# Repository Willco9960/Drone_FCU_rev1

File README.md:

# Drone MCU

I'm building a drone flight controller from scratch and using it to explore neural networks along the way. The long-term goal is a small autonomous drone that can track a person, follow them and orbit around them. First though, I need a board that works on my desk and tells me which way is up.

This is a university project and a work in progress.

## How I built it

I designed and routed the board myself in KiCad. I also used an AI agent connected through an MCP to help choose parts and check the schematic and routing as I went.

## The plan

V1 is a USB-powered development board built around an STM32H743 and an IMU, the sensor that measures movement and rotation. The idea is to read that sensor on the board, send live data to a computer and show the board's orientation in a window.

I also want to train a small neural network in simulation and run it on the MCU. The computer will show what the sensor is doing alongside the network's predicted correction so I can see what it's learning before motors get involved.

The V1 testbench board is currently in production. Once it arrives, I'll start testing it on the bench. It doesn't control motors or fly. Later versions will need flight hardware, reliable stabilization, a camera, tracking and plenty of testing before they become the autonomous drone I'm aiming for.

## Where things are

- [Drone_MCU_V1](Drone_MCU_V1/) has the current KiCad project. Open [Drone_MCU_V1.kicad_pro](Drone_MCU_V1/Drone_MCU_V1.kicad_pro) to see the schematic and PCB.
- [V1 plan](Drone_MCU_V1/V1_PLAN.md) explains the goals and the work still to do.
- [Manufacturing and assembly files](Drone_MCU_V1/manufacturing/2026-11-08-quote/) contain the quote files, parts list and assembly research. The files in this folder are marked quote only, so check the review before using them for an order.
- [Reviews](Drone_MCU_V1/reviews/) contain saved design checks and notes from the board review.
- [REV_1](REV_1/) is the earlier flight controller design. I'm keeping it around as a reference while V1 gets its own fresh start.

[DECISIONS.md](DECISIONS.md) keeps the project decisions and open questions. [AGENTS.md](AGENTS.md) has context for anyone using an AI agent to help with the project.

## PCB images

Here's a look at the V1 board in KiCad before it heads to the bench.

## What's next

Test the board when it arrives, read the IMU, stream the data to a computer and build the live orientation display. After that it's time to get a neural network trained in simulation and see what the MCU can do with it.

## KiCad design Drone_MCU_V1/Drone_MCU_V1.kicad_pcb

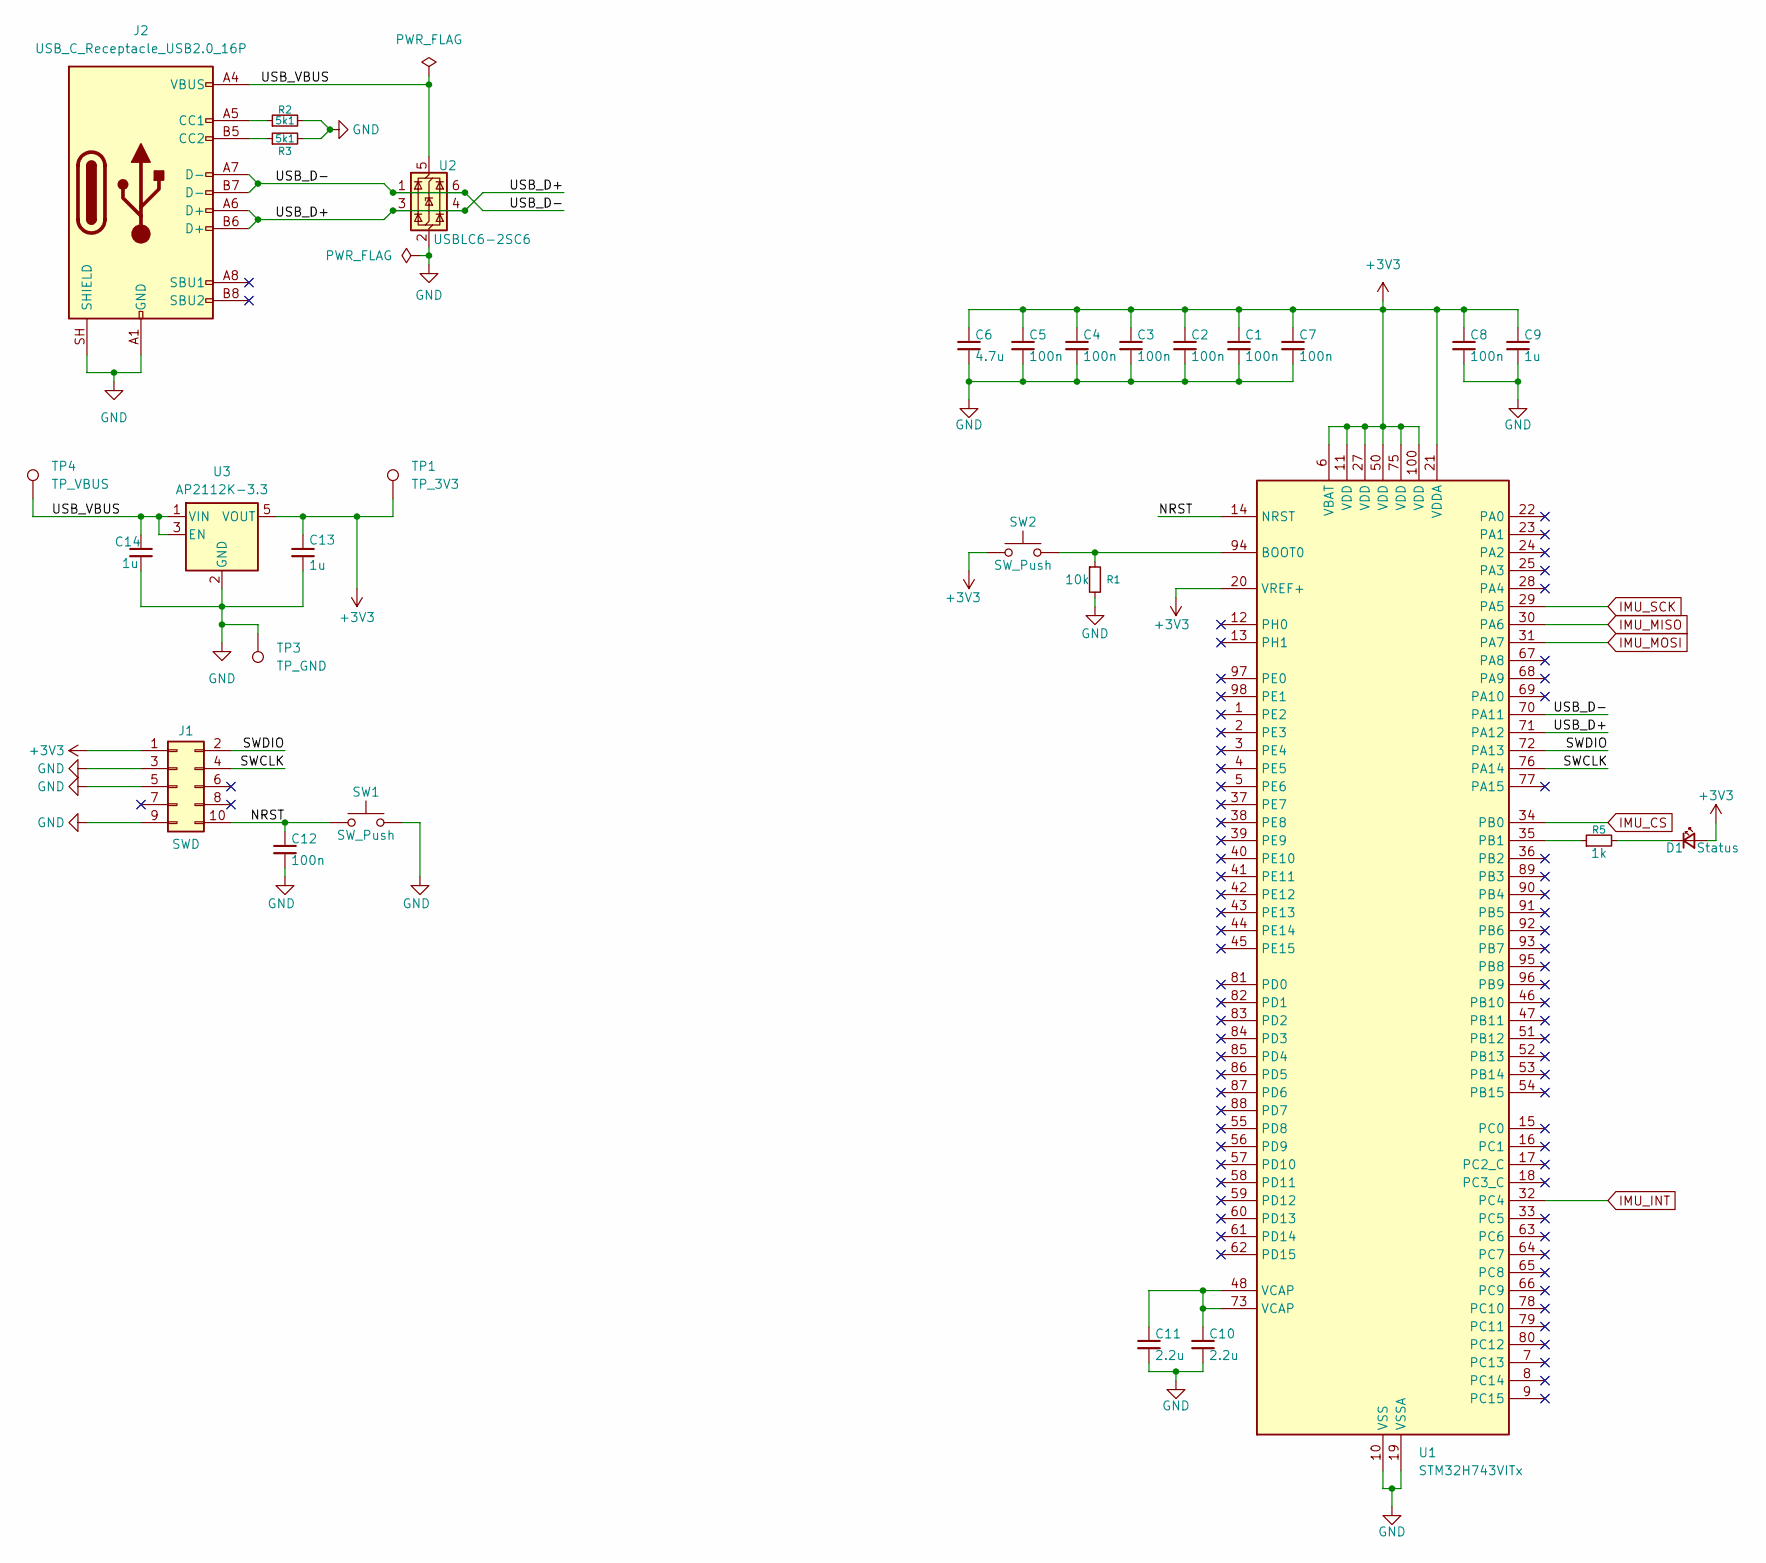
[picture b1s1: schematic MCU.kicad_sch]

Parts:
C1, C2, C3, C4, C5, C7, C8, C12: 100n; C_0805_2012Metric
C6: 4.7u; C_1206_3216Metric
C9, C13, C14: 1u; C_0805_2012Metric
C10, C11: 2.2u; C_1206_3216Metric
D1: Status; LED_0805_2012Metric
J1: SWD; PinHeader_2x05_P2.54mm_Vertical
J2: USB_C_Receptacle_USB2.0_16P; USB_C_Receptacle_HRO_TYPE-C-31-M-12
R1: 10k; R_0805_2012Metric
R2, R3: 5k1; R_0805_2012Metric
R5: 1k; R_0805_2012Metric
SW1, SW2: SW_Push; SW_SPST_B3U-1000P
TP1: TP_3V3; TestPoint_Pad_D1.5mm
TP3: TP_GND; TestPoint_Pad_D1.5mm
TP4: TP_VBUS; TestPoint_Pad_D1.5mm
U1: STM32H743VITx; LQFP-100_14x14mm_P0.5mm
U2: USBLC6-2SC6; SOT-23-6
U3: AP2112K-3.3; SOT-23-5

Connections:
+3V3: C1.1, C2.1, C3.1, C4.1, C5.1, C6.1, C7.1, C8.1, C9.1, C13.1, D1.2 (A), J1.1, SW2.1, TP1.1 (1_1), U1.6 (VBAT), U1.11 (VDD), U1.20 (VREF+), U1.21 (VDDA), U1.27 (VDD), U1.50 (VDD), U1.75 (VDD), U1.100 (VDD), U3.5 (VOUT); also elsewhere on the board
/MCU/NRST: C12.1, J1.10, SW1.1, U1.14 (NRST)
/MCU/SWCLK: J1.4, U1.76 (PA14)
/MCU/SWDIO: J1.2, U1.72 (PA13)
/MCU/USB_D+: J2.A6 (D+), J2.B6 (D+), U1.71 (PA12), U2.3 (I/O2), U2.4 (I/O2)
/MCU/USB_D-: J2.A7 (D-), J2.B7 (D-), U1.70 (PA11), U2.1 (I/O1), U2.6 (I/O1)
/MCU/USB_VBUS: C14.1, J2.A4 (VBUS), J2.A9 (VBUS), J2.B4 (VBUS), J2.B9 (VBUS), TP4.1 (1_1), U2.5 (VBUS), U3.1 (VIN), U3.3 (EN)
GND: C1.2, C2.2, C3.2, C4.2, C5.2, C6.2, C7.2, C8.2, C9.2, C10.2, C11.2, C12.2, C13.2, C14.2, J1.3, J1.5, J1.9, J2.A1 (GND), J2.A12 (GND), J2.B1 (GND), J2.B12 (GND), J2.SH (SHIELD), R1.2, R2.2, R3.2, SW1.2, TP3.1 (1_1), U1.10 (VSS), U1.19 (VSSA), U1.26 (VSS), U1.49 (VSS), U1.74 (VSS), U1.99 (VSS), U2.2 (GND), U3.2 (GND); also elsewhere on the board
IMU_CS: U1.34 (PB0); also elsewhere on the board
IMU_INT: U1.32 (PC4); also elsewhere on the board
IMU_MISO: U1.30 (PA6); also elsewhere on the board
IMU_MOSI: U1.31 (PA7); also elsewhere on the board
IMU_SCK: U1.29 (PA5); also elsewhere on the board
unnamed: C10.1, C11.1, U1.48 (VCAP), U1.73 (VCAP)
unnamed: D1.1 (K), R5.2
unnamed: J2.A5 (CC1), R2.1
unnamed: J2.B5 (CC2), R3.1
unnamed: R1.1, SW2.2, U1.94 (BOOT0)
unnamed: R5.1, U1.35 (PB1)

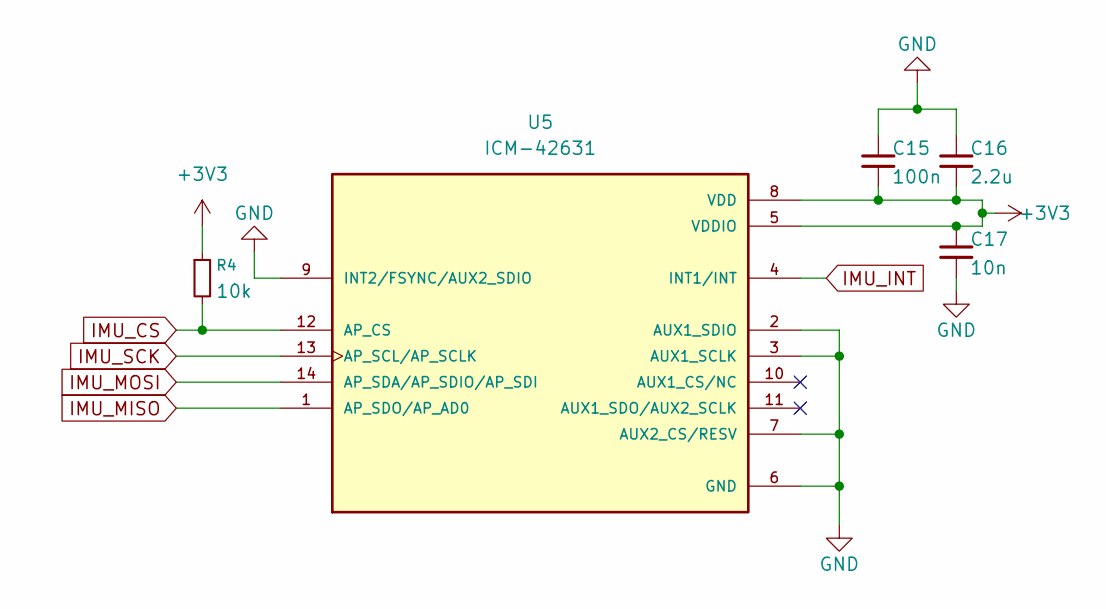
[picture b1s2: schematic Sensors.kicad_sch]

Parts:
C15: 100n; C_0805_2012Metric
C16: 2.2u; C_0805_2012Metric
C17: 10n; C_0805_2012Metric
R4: 10k; R_0805_2012Metric
U5: ICM-42631; ICM-42631_TDK_LGA14_trial; PARTREV 1.2

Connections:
+3V3: C15.2, C16.2, C17.1, R4.1, U5.5 (VDDIO), U5.8 (VDD); also elsewhere on the board
GND: C15.1, C16.1, C17.2, U5.2 (AUX1_SDIO), U5.3 (AUX1_SCLK), U5.6 (GND), U5.7 (AUX2_CS/RESV), U5.9 (INT2/FSYNC/AUX2_SDIO); also elsewhere on the board
IMU_CS: R4.2, U5.12 (AP_CS); also elsewhere on the board
IMU_INT: U5.4 (INT1/INT); also elsewhere on the board
IMU_MISO: U5.1 (AP_SDO/AP_AD0); also elsewhere on the board
IMU_MOSI: U5.14 (AP_SDA/AP_SDIO/AP_SDI); also elsewhere on the board
IMU_SCK: U5.13 (AP_SCL/AP_SCLK); also elsewhere on the board

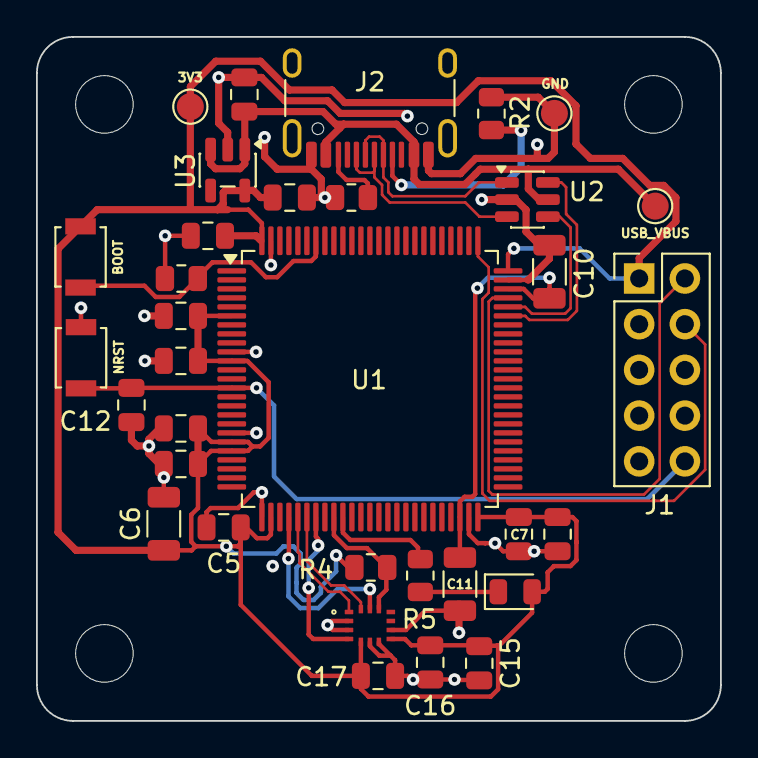
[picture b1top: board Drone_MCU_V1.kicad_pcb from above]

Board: 4 copper layers, 38.0 x 38.0 mm, 38 parts (0 on the bottom side), 19 nets.

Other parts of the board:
MH1, MH2, MH3, MH4: MountingHole_3.2mm_M3

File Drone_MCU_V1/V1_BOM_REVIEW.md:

# V1 preliminary parts and assembly review

Updated 2026-11-03. This is a candidate BOM for the existing, unrouted USB-powered bench prototype. It is **not an assembly order or a JLCPCB stock reservation**. Retail LCSC availability and JLCPCB assembly availability are separate, change with time, and must be confirmed in the actual JLCPCB order/quote. The MCP JLCPCB database contained no catalog data for these lookups. The schematic does not yet embed verified LCSC fields; do not export a final assembly BOM from it without completing those fields and checking orientations and footprints.

| References | Qty | Candidate part / LCSC | Review |
|---|---:|---|---|
| U1 | 1 | ST STM32H743VIT6 / [C114409](https://www.lcsc.com/product-detail/C114409.html) | LQFP-100, 14 x 14 mm. Confirm silicon revision and startup clock/USB firmware. |
| U2 | 1 | ST USBLC6-2SC6 / [C7519](https://www.lcsc.com/product-detail/C7519.html) | SOT-23-6. Verify exact ST part/assembly placement and USB connector-to-protection-to-MCU routing. |
| U3 | 1 | Diodes Inc. AP2112K-3.3TRG1 / [C51118](https://www.lcsc.com/product-detail/C51118.html) | SOT-23-5. Thermal and USB-current limits remain a design gate; see below. |
| U5 | 1 | TDK ICM-42631 / [C41432121](https://www.lcsc.com/product-detail/C41432121.html) | LGA-14. Mask/stencil/assembly acceptance open; do not approve assembly yet. |
| C1–C5, C7, C8, C12, C15 | 9 | Samsung CL21B104KBCNNNC / [C1711](https://www.lcsc.com/product-detail/C1711.html) | 100 nF, 50 V, X7R, 0805, ±10%. |
| C6 | 1 | KEMET C1206C475K4RACTU / [C2167346](https://www.lcsc.com/product-detail/C2167346.html) | 4.7 µF, 16 V, X7R, 1206, ±10%. Effective value at 3.3 V and operating temperature not yet verified. |
| C9, C13, C14 | 3 | Samsung CL21B105KAFNNNE / [C116352](https://www.lcsc.com/product-detail/C116352.html) | 1 µF, 25 V, X7R, 0805. Effective capacitance at 3.3/5 V and LDO stability not yet verified. |
| C10, C11 | 2 | Murata GCM31CR71H225KA55L / [C126604](https://www.lcsc.com/product-detail/C126604.html) | 2.2 µF, 50 V, X7R, 1206. Strong VCAP candidate; manufacturer-specific guaranteed ESR versus frequency, DC bias and temperature still require confirmation. |
| C16 | 1 | Samsung CL21B225KAFNNNE / [C19110](https://www.lcsc.com/product-detail/C19110.html) | 2.2 µF, 25 V, X7R, 0805. Check effective value and TDK requirements. |
| C17 | 1 | Samsung CL21B103KBANNNC / [C1710](https://www.lcsc.com/product-detail/C1710.html) | 10 nF, 50 V, X7R, 0805. Check against the device configuration and TDK guidance. |
| R1, R4 | 2 | UNI-ROYAL 0805W8F1002T5E / [C17414](https://www.lcsc.com/product-detail/C17414.html) | 10 kΩ 1%, 0805. |
| R2, R3 | 2 | UNI-ROYAL 0805W8F5101T5E / [C27834](https://www.lcsc.com/product-detail/C27834.html) | 5.1 kΩ 1%, 0805, independent USB-C CC pull-downs. |
| R5 | 1 | UNI-ROYAL 0805W8F1001T5E / [C17513](https://www.lcsc.com/product-detail/C17513.html) | 1 kΩ 1%, 0805. |
| D1 | 1 | KENTO KT-0805R / [C2295](https://www.lcsc.com/product-detail/C2295.html) | Red 0805 LED; verify component polarity against footprint pin 1 and assembler orientation before release. |
| J2 | 1 | HRO TYPE-C-31-M-12 / [C165948](https://www.lcsc.com/product-detail/C165948.html) | Confirm exact footprint, shell-tab drills and JLCPCB treatment of through-hole shell tabs. |
| SW1, SW2 | 2 | Omron B3U-1000P / [C231329](https://www.lcsc.com/product-detail/C231329.html) | SMD switches; verify footprint and assembly availability. |
| J1 | 1 | CJT A2541WV-2x5P / [C225520](https://www.lcsc.com/product-detail/C225520.html) | 2x5 2.54 mm through-hole header. Verify mating cable/pin numbering; through-hole assembly may require separate service or hand soldering. |
| TP1, TP3, TP4 | 3 | PCB test pads | No component to purchase or assemble. |

## VCAP

ST [AN4938](https://www.st.com/resource/en/application_note/an4938-getti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 specifies two 2.2 µF ceramic capacitors, each below 100 mΩ ESR, with the VCAP pins tied. A published [Infineon reference](https://www.infineon.com/export/sites/default/cn/partners/pa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 identifies the Murata GCM31CR71H225KA55 family as an automotive counterpart of the GRM31 2.2 µF / 50 V part and illustrates approximately 5 mΩ ESR at 400 kHz and about 1.7 µF at 18 V bias. These are example/typical curves, not a guaranteed upper ESR bound across frequency, temperature and lot. The MCU nominal core voltage is much lower, but specific curves, applicable frequency and ST minimum effective capacitance must be confirmed before marking this production-approved. Place the capacitors close to their VCAP connections and provide a short return.

## Power and thermal budget

For the current 5 V USB-to-3.3 V LDO, approximate dissipation is **P = (5 − 3.3) × I**, ignoring small quiescent current. At 150 mA that is 0.255 W; at 226 mA it is 0.384 W; at 348 mA it is 0.592 W. The AP2112 SOT25 data sheet gives a reference junction-to-ambient thermal resistance of 184 °C/W; those points imply rises of about 47 °C, 71 °C and 109 °C under that test condition, not a measured temperature on this PCB. Actual PCB copper, ambient, airflow, USB input tolerance and load determine the result. The 600 mA current rating does not prove that the package can dissipate the corresponding heat.

ST's STM32H743 datasheet shows 480 MHz operation with all peripherals enabled around 226 mA typical and 348 mA maximum at 25 °C junction for the specified conditions (rev V table). These are examples, not this firmware's measured draw; additional IMU, LEDs, I/O and leakage add load. At the 348 mA example the LDO thermal margin can be poor, and MCU maxima vary strongly with junction temperature and workload. Firmware must start conservatively, respect source-advertised/USB configured current, and remain within a measured thermal/current budget. Do not claim USB or 480 MHz operation is validated without testing. If full workload exceeds the budget, redesign the regulator/power path before ordering rather than assuming the 600 mA label is sufficient.

Sources: [ST STM32H743 datasheet](https://www.st.com/resource/en/datasheet/stm32h743vi.pdf), [Diodes AP2112 datasheet](https://www.diodes.com/datasheet/download/AP2112.pdf), [Microchip USB power overview](https://developerhelp.microchip.com/xwiki/bin/view/applicati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

## IMU mask and stencil

[TDK AN-000393](https://invensense.tdk.com/wp-content/uploads/2023/05/an-000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 recommends non-solder-mask-defined lands and mask openings 0.10 mm larger in each dimension, and suggests a 90% stencil-opening-to-land ratio under standard conditions. Current PCB has full-size paste and +0.05 mm mask expansion per side; some mask webs measure approximately 0.04–0.085 mm. JLCPCB's [capabilities](https://jlcpcb.com/capabilities/pcb-capabilities) cite 0.10 mm mask bridges for 1 oz standard colors and a 1:1 opening capability, while its [mask guide](https://jlcpcb.com/blog/basic-design-of-solder-mask) notes standard processing can modify narrow webs. Shrinking to 1:1 without review would conflict with TDK's nominal NSMD recommendation; ganging openings changes bridging and exposed-copper behavior. Need a specific JLCPCB/TDK-approved mask, stencil and assembly plan or a verified alternative before fabrication. No manufacturer confirmation has been obtained.

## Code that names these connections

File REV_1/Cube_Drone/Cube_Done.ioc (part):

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Mcu.Name=STM32F722V(C-E)Tx
Mcu.Package=LQFP100
Mcu.UserName=STM32F722VETx
PA11.Mode=Device_Only
PA11.Signal=USB_OTG_FS_DM
PA12.Mode=Device_Only
PA12.Signal=USB_OTG_FS_DP
PA13.Mode=Serial_Wire
PA13.Signal=SYS_JTMS-SWDIO
PA14.Mode=Serial_Wire
PA14.Signal=SYS_JTCK-SWCLK
RCC.HSE_VALUE=25000000
RCC.SYSCLKFreq_VALUE=16000000
board=custom

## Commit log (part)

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2026-02-28 added usb otg and swd
2026-03-14 Added IMU schematic block
